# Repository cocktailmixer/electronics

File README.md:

# electronics

still under construction

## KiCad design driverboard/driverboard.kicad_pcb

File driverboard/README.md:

# Driverboard
### What is the status?
- design v01: complete
- schematic v01: complete
- layout rev. A: complete
- gerbers and bom: todo
- testing: todo
### What does it do?
The driverboard is connected by a ribbon cable and a seperate power cable to the controllerboard. Each driverboard can drive eight resistive or inductive loads like pumps or valves up to 600mA per channel. Multiple driverboards can be connected in series after another, the power and data gets passed along to the next driverboard.

The controllerboard is an SPI bus master and passes data to the driverboards which are connected in series as an SPI bus daisy-chain. The end of the chain is automatically recognized by the hardware and the fault reporting data looped back to the master.

The driver chip used is the ON Semi NCV7240 which features fault reporting (overload and overtemperature protection, open load / short to ground and SPI frame error detection), internal output clamping diodes and a 3.3V / 5V compatible SPI interface.

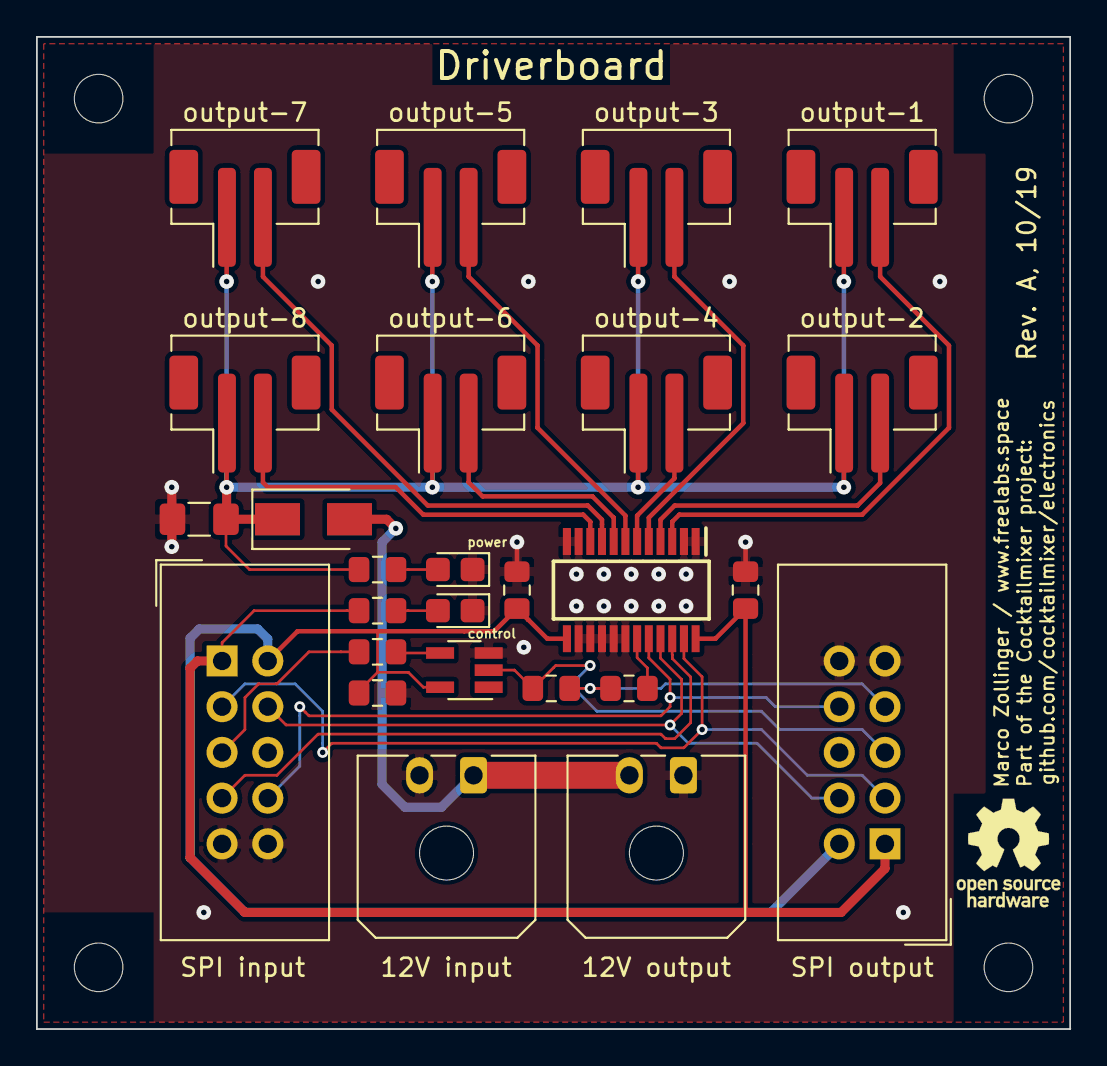
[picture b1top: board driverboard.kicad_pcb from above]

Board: 2 copper layers, 57.4 x 55.1 mm, 30 parts (0 on the bottom side), 24 nets.

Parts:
C1, C2, C3: 100n; C_0805_2012Metric_Pad1.15x1.40mm_HandSolder
C4: 10u; C_1206_3216Metric_Pad1.42x1.75mm_HandSolder
D1: power; LED_0805_2012Metric_Castellated
D2: control; LED_0805_2012Metric_Castellated
D3: MBRA340; D_SMA
IC1: NCV7240ADPR2G; SOP65P600X175-24N
J1: output-1; JST_PH_B2B-PH-SM4-TB_1x02-1MP_P2.00mm_Vertical
J2: output-2; JST_PH_B2B-PH-SM4-TB_1x02-1MP_P2.00mm_Vertical
J3: output-3; JST_PH_B2B-PH-SM4-TB_1x02-1MP_P2.00mm_Vertical
J4: output-4; JST_PH_B2B-PH-SM4-TB_1x02-1MP_P2.00mm_Vertical
J5: output-5; JST_PH_B2B-PH-SM4-TB_1x02-1MP_P2.00mm_Vertical
J6: output-6; JST_PH_B2B-PH-SM4-TB_1x02-1MP_P2.00mm_Vertical
J7: output-7; JST_PH_B2B-PH-SM4-TB_1x02-1MP_P2.00mm_Vertical
J8: output-8; JST_PH_B2B-PH-SM4-TB_1x02-1MP_P2.00mm_Vertical
J9: SPI input; IDC-Header_2x05_P2.54mm_Vertical
J10: SPI output; IDC-Header_2x05_P2.54mm_Vertical
J11: 12V input; Molex_Micro-Fit_3.0_43650-0200_1x02_P3.00mm_Horizontal
J12: 12V output; Molex_Micro-Fit_3.0_43650-0200_1x02_P3.00mm_Horizontal
MH1, MH2, MH3, MH4: MountingHole_2.7mm_M2.5
R1, R3: 100; R_0805_2012Metric_Pad1.15x1.40mm_HandSolder
R2, R4: 2k0; R_0805_2012Metric_Pad1.15x1.40mm_HandSolder
R5: 560; R_0805_2012Metric_Pad1.15x1.40mm_HandSolder
U1: 74LVC1G34; SOT-23-5_HandSoldering

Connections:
+5V: C1.1, IC1.24, J9.1, J10.1, R5.1
+12V: C4.1, D3.1, J1.1, J2.1, J3.1, J4.1, J5.1, J6.1, J7.1, J8.1, R4.1
GND: C1.2, C2.2, C3.2, C4.2, D1.1, D2.1, IC1.1, IC1.2, IC1.11, IC1.12, IC1.14, IC1.15, IC1.16, IC1.17, IC1.18, J9.9, J9.10, J10.9, J10.10, J11.2, J12.1, U1.3
unnamed: D1.2, R4.2
unnamed: D2.2, R5.2
unnamed: D3.2, J11.1, J12.2
unnamed: IC1.3, J1.2
unnamed: IC1.4, J2.2
unnamed: IC1.5, J3.2
unnamed: IC1.6, J4.2
unnamed: IC1.7, J5.2
unnamed: IC1.8, J6.2
unnamed: IC1.9, J7.2
unnamed: IC1.10, J8.2
unnamed: IC1.19, R1.2
unnamed: IC1.20, J9.8, J10.8
unnamed: IC1.21, J9.4, J10.4
unnamed: IC1.22, J9.7
unnamed: IC1.23, J9.3, J10.3
unnamed: J9.5, R3.2
unnamed: J10.5, R2.2, U1.2
unnamed: J10.7, R1.1, R2.1
unnamed: R3.1, U1.4
VCC: C2.1, C3.1, IC1.13, J9.2, J10.2, U1.5

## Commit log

2019-07-12 driverboard initial commit
2019-07-12 add gitignore
2019-07-12 extend gitignore for tmp files
2019-07-12 allow .net files for portability
2019-07-13 add driver and valve connectors
2019-07-13 wire data input/output connectors
2019-07-13 improved readability
2019-07-13 schematic wiring complete w/o buffers
2019-07-13 added daisy-chain auto-termination
2019-07-14 finalize v01 design
2019-07-14 License by CC BY-SA 4.0
2019-07-15 Add project description
2019-07-15 Update project description
2019-07-23 add optional crystal oscillator
2019-07-23 add analog AVR supply and raspi header
2019-07-24 add raspi isp and uart bus
2019-07-25 add spi multiplexer and reset circuitry
2019-07-27 add 5v buck converter draft
2019-07-29 add power switch, gate driver and current sense
2019-07-30 add emergency switch logic
2019-09-02 remove MUX and use soft-SPI for driverboard
2019-09-02 add emergency shutdown circuitry
2019-09-04 complete emergency shutdown circuitry
2019-09-04 add I2C circuitry
2019-09-04 add driverboard interface
2019-09-06 minor and cosmetic improvements
2019-10-07 add driverboard component libraries
2019-10-08 assign driverboard footprints
2019-10-08 generate netlist
2019-10-08 add design rules, start placement
2019-10-08 route output traces
2019-10-08 start routing data connectors
2019-10-08 finish routing signals
2019-10-08 add ground polygon fill
2019-10-11 correct output power connector polarity
2019-10-11 finish routing
2019-10-11 improve routing
2019-10-13 add reverse polarity protection
2019-10-14 add mounting holes
2019-10-15 add labels
2019-10-16 add TPS56339 library
